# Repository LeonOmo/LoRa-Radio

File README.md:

# LoRa-Puck

A 4 Layered LoRa puck powered by the RP2040 microcontroller.

## Features

- Microcontroller: RP2040
- Trasnceiver: SX1262 for long rage communication
- Frequency: European 868 MHz 
- PCB: 4 Layers

## Why does this project exist?

I wanted to dive abit into radios / radio frequency / radio design... and so i built a lora puck with the given guide.

## BOM

| Component | Function | LCSC Number |
| :--- | :--- | :--- |
| RP 2040 | Microcontroller | |
| SX1262 | Radio Transciever | |
| Johanson 0900FM15D0039 | IPD  | |

## Tools

- PCB Design: KiCAD
- Guide referance: https://blueprint.hackclub.com/starter-projects/lora

## Schematic

## PCB

## Extra

I didnt really understand all the RF theory behind it too well but putting it together routing the tracks and making sure everything connects properly was still a great learning experience.

Credits
- https://blueprint.hackclub.com/starter-projects/lora

## Bonus

Nothing yet.

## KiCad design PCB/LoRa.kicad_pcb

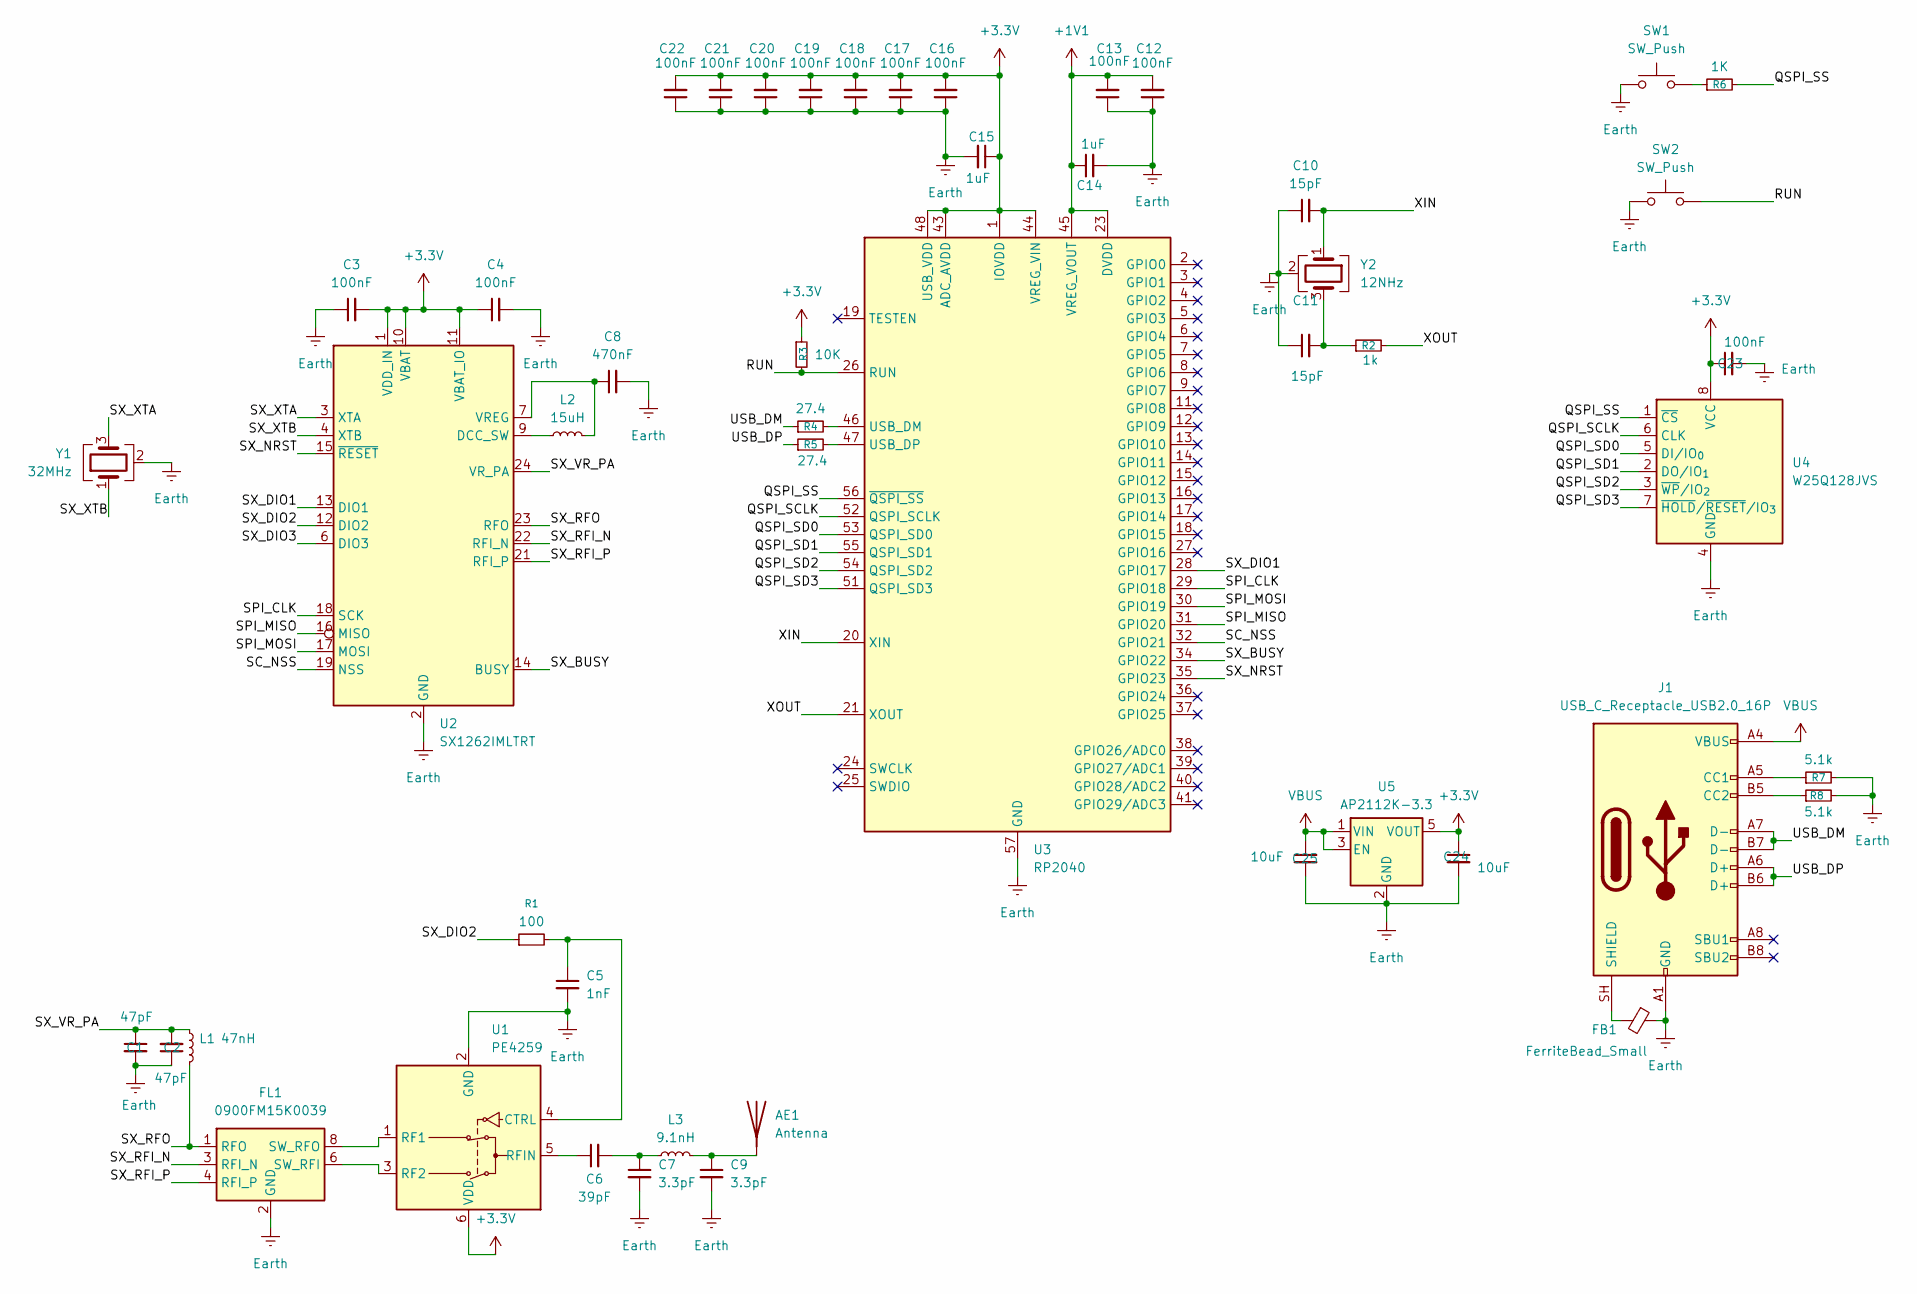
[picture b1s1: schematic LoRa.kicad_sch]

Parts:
AE1: Antenna; PinSocket_1x01_P2.54mm_Vertical
C1, C2: 47pF; C_0402_1005Metric
C3, C4, C12, C13, C16, C17, C18, C19, C20, C21, C22, C23: 100nF; C_0402_1005Metric
C5: 1nF; C_0402_1005Metric
C6: 39pF; C_0402_1005Metric
C7, C9: 3.3pF; C_0402_1005Metric
C8: 470nF; C_0402_1005Metric
C10, C11: 15pF; C_0402_1005Metric
C14, C15: 1uF; C_0402_1005Metric
C24, C25: 10uF; C_0402_1005Metric
FB1: FerriteBead_Small; L_0402_1005Metric
FL1: 0900FM15K0039; Balun_Johanson_0900FM15K0039
J1: USB_C_Receptacle_USB2.0_16P; USB_C_Receptacle_GCT_USB4105-xx-A_16P_TopMnt_Horizontal
L1: 47nH; L_0402_1005Metric
L2: 15uH; L_0402_1005Metric
L3: 9.1nH; L_0402_1005Metric
R1: 100; R_0402_1005Metric
R2: 1k; R_0402_1005Metric
R3: 10K; R_0402_1005Metric
R4, R5: 27.4; R_0402_1005Metric
R6: 1K; R_0402_1005Metric
R7, R8: 5.1k; R_0402_1005Metric
SW1, SW2: SW_Push; SW_Tactile_SPST_NO_Straight_CK_PTS636Sx25SMTRLFS
U1: PE4259; SOT-363_SC-70-6
U2: SX1262IMLTRT; QFN-24-1EP_4x4mm_P0.5mm_EP2.6x2.6mm
U3: RP2040; QFN-56-1EP_7x7mm_P0.4mm_EP3.2x3.2mm
U4: W25Q128JVS; SOIC-8_5.3x5.3mm_P1.27mm
U5: AP2112K-3.3; SOT-23-5
Y1: 32MHz; Crystal_SMD_3225-4Pin_3.2x2.5mm
Y2: 12NHz; Crystal_SMD_Abracon_ABM8G-4Pin_3.2x2.5mm

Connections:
+1V1: C12.2, C13.2, C14.1, U3.23 (DVDD), U3.45 (VREG_VOUT), U3.50 (DVDD)
+3.3V: C3.2, C4.1, C15.1, C16.2, C17.2, C18.2, C19.2, C20.2, C21.2, C22.2, C23.1, C24.1, R3.1, U1.6 (VDD), U2.1 (VDD_IN), U2.10 (VBAT), U2.11 (VBAT_IO), U3.1 (IOVDD), U3.10 (IOVDD), U3.22 (IOVDD), U3.33 (IOVDD), U3.42 (IOVDD), U3.43 (ADC_AVDD), U3.44 (VREG_VIN), U3.48 (USB_VDD), U3.49 (IOVDD), U4.8 (VCC), U5.5 (VOUT)
/QSPI_SCLK: U3.52 (QSPI_SCLK), U4.6 (CLK)
/QSPI_SD0: U3.53 (QSPI_SD0), U4.5 (DI/IO_{0})
/QSPI_SD1: U3.55 (QSPI_SD1), U4.2 (DO/IO_{1})
/QSPI_SD2: U3.54 (QSPI_SD2), U4.3 (~WP/IO_{2})
/QSPI_SD3: U3.51 (QSPI_SD3), U4.7 (~HOLD/~RESET/IO_{3})
/QSPI_SS: R6.2, U3.56 (~QSPI_SS), U4.1 (~CS)
/RUN: R3.2, SW2.2, U3.26 (RUN)
/SC_NSS: U2.19 (NSS), U3.32 (GPIO21)
/SPI_CLK: U2.18 (SCK), U3.29 (GPIO18)
/SPI_MISO: U2.16 (MISO), U3.31 (GPIO20)
/SPI_MOSI: U2.17 (MOSI), U3.30 (GPIO19)
/SX_BUSY: U2.14 (BUSY), U3.34 (GPIO22)
/SX_DIO1: U2.13 (DIO1), U3.28 (GPIO17)
/SX_DIO2: R1.1, U2.12 (DIO2)
/SX_DIO3: U2.6 (DIO3)
/SX_NRST: U2.15 (~RESET), U3.35 (GPIO23)
/SX_RFI_N: FL1.3 (RFI_N), U2.22 (RFI_N)
/SX_RFI_P: FL1.4 (RFI_P), U2.21 (RFI_P)
/SX_RFO: FL1.1 (RFO), L1.2, U2.23 (RFO)
/SX_VR_PA: C1.1, C2.2, L1.1, U2.24 (VR_PA)
/SX_XTA: U2.3 (XTA), Y1.3
/SX_XTB: U2.4 (XTB), Y1.1
/USB_DM: J1.A7 (D-), J1.B7 (D-), R4.1
/USB_DP: J1.A6 (D+), J1.B6 (D+), R5.1
/XIN: C10.2, U3.20 (XIN), Y2.1
/XOUT: R2.2, U3.21 (XOUT)
Earth: C1.2, C2.1, C3.1, C4.2, C5.2, C7.2, C8.2, C9.2, C10.1, C11.1, C12.1, C13.1, C14.2, C15.2, C16.1, C17.1, C18.1, C19.1, C20.1, C21.1, C22.1, C23.2, C24.2, C25.2, FB1.1, FL1.2 (GND), FL1.5 (GND), FL1.7 (GND), FL1.9 (GND), FL1.10 (GND), J1.A1 (GND), J1.A12 (GND), J1.B1 (GND), J1.B12 (GND), R7.2, R8.2, SW1.1, SW2.1, U1.2 (GND), U2.2 (GND), U2.5 (GND), U2.8 (GND), U2.20 (GND), U2.25 (GND), U3.57 (GND), U4.4 (GND), U5.2 (GND), Y1.2 (G), Y1.4 (G), Y2.2 (G), Y2.4 (G)
unnamed: AE1.1 (A_1), C9.1, L3.2
unnamed: C6.2, C7.1, L3.1
unnamed: C11.2, R2.1, Y2.3
unnamed: FL1.6 (SW_RFI), U1.3 (RF2)
unnamed: FL1.8 (SW_RFO), U1.1 (RF1)
unnamed: J1.A5 (CC1), R7.1
unnamed: J1.B5 (CC2), R8.1
unnamed: FB1.2, J1.SH (SHIELD)
unnamed: R6.1, SW1.2
unnamed: C5.1, R1.2, U1.4 (CTRL)
unnamed: C6.1, U1.5 (RFIN)
unnamed: L2.1, U2.9 (DCC_SW)
unnamed: C8.1, L2.2, U2.7 (VREG)
unnamed: R4.2, U3.46 (USB_DM)
unnamed: R5.2, U3.47 (USB_DP)
VBUS: C25.1, J1.A4 (VBUS), J1.A9 (VBUS), J1.B4 (VBUS), J1.B9 (VBUS), U5.1 (VIN), U5.3 (EN)

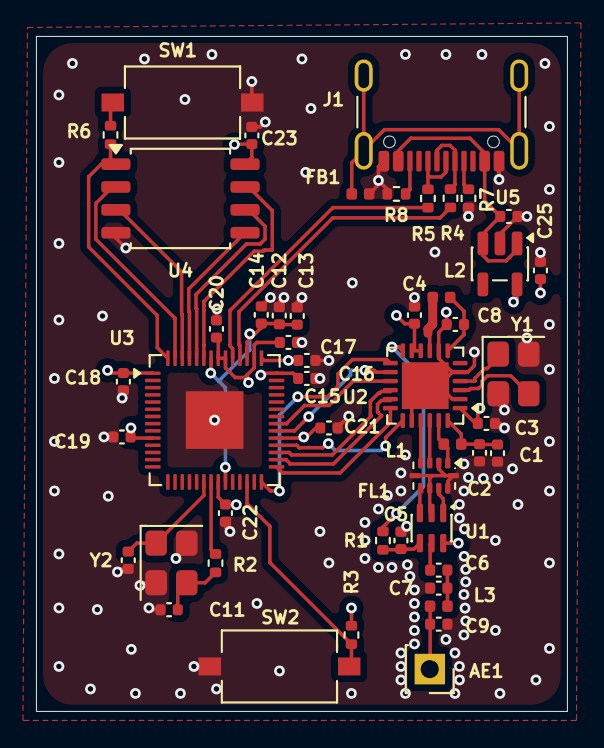
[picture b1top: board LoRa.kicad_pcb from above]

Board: 4 copper layers, 29.5 x 37.5 mm, 49 parts (0 on the bottom side), 44 nets.

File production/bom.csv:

Designator,Footprint,Quantity,Value,LCSC Part #
AE1,PinSocket_1x01_P2.54mm_Vertical,1,Antenna,
"C1, C2",0402,2,47pF,
"C10, C11",0402,2,15pF,
"C12, C13, C16, C17, C18, C19, C20, C21, C22, C23, C3, C4",0402,12,100nF,
"C14, C15",0402,2,1uF,
"C24, C25",0402,2,10uF,
C5,0402,1,1nF,
C6,0402,1,39pF,
"C7, C9",0402,2,3.3pF,
C8,0402,1,470nF,
FB1,0402,1,FerriteBead_Small,
FL1,Balun_Johanson_0900FM15K0039,1,0900FM15K0039,
J1,USB_C_Receptacle_GCT_USB4105-xx-A_16P_TopMnt_Horizontal,1,USB_C_Receptacle_USB2.0_16P,
L1,0402,1,47nH,
L2,0402,1,15uH,
L3,0402,1,9.1nH,
R1,0402,1,100,
"R2, R6",0402,2,1k,
R3,0402,1,10K,
"R4, R5",0402,2,27.4,
"R7, R8",0402,2,5.1k,
"SW1, SW2",SW_Tactile_SPST_NO_Straight_CK_PTS636Sx25SMTRLFS,2,SW_Push,
U1,SOT-363_SC-70-6,1,PE4259,
U2,QFN-24-1EP_4x4mm_P0.5mm_EP2.6x2.6mm,1,SX1262IMLTRT,
U3,QFN-56-1EP_7x7mm_P0.4mm_EP3.2x3.2mm,1,RP2040,
U4,SOIC-8_5.3x5.3mm_P1.27mm,1,W25Q128JVS,
U5,SOT-23-5,1,AP2112K-3.3,
Y1,Crystal_SMD_3225-4Pin_3.2x2.5mm,1,32MHz,
Y2,Crystal_SMD_Abracon_ABM8G-4Pin_3.2x2.5mm,1,12NHz,
